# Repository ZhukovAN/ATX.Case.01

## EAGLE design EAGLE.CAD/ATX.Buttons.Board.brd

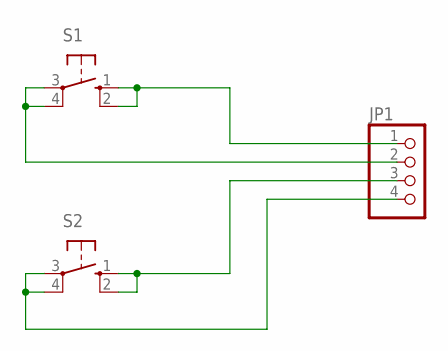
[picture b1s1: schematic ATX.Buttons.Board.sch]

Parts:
JP1: PINHD-1X4/90; 1X04/90
S1, S2: 10-XX; B3F-10XX

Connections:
unnamed: JP1.1, S1.1 (S), S1.2 (S1)
unnamed: JP1.3, S2.1 (S), S2.2 (S1)
unnamed: JP1.4, S2.3, S2.4 (P1)
unnamed: JP1.2, S1.3, S1.4 (P1)

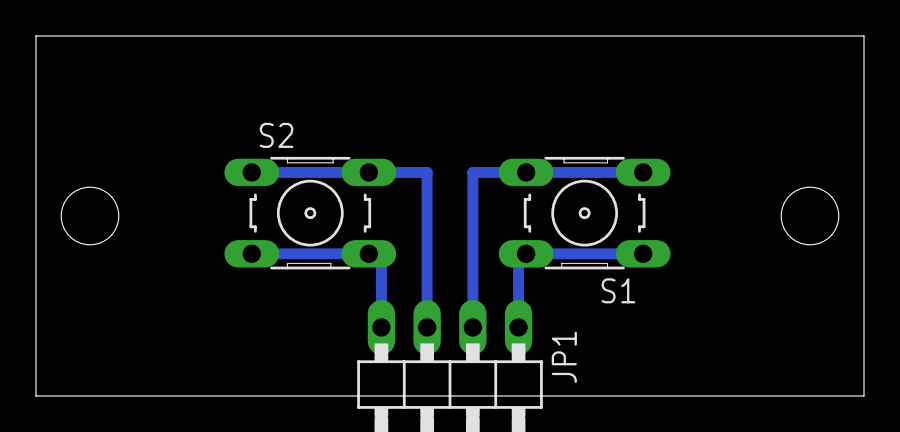
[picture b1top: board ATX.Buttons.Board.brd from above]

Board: 2 copper layers, 46.0 x 20.0 mm, 3 parts (0 on the bottom side), 4 nets.

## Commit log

2018-05-02 20180502
2018-05-02 Eagle files added
